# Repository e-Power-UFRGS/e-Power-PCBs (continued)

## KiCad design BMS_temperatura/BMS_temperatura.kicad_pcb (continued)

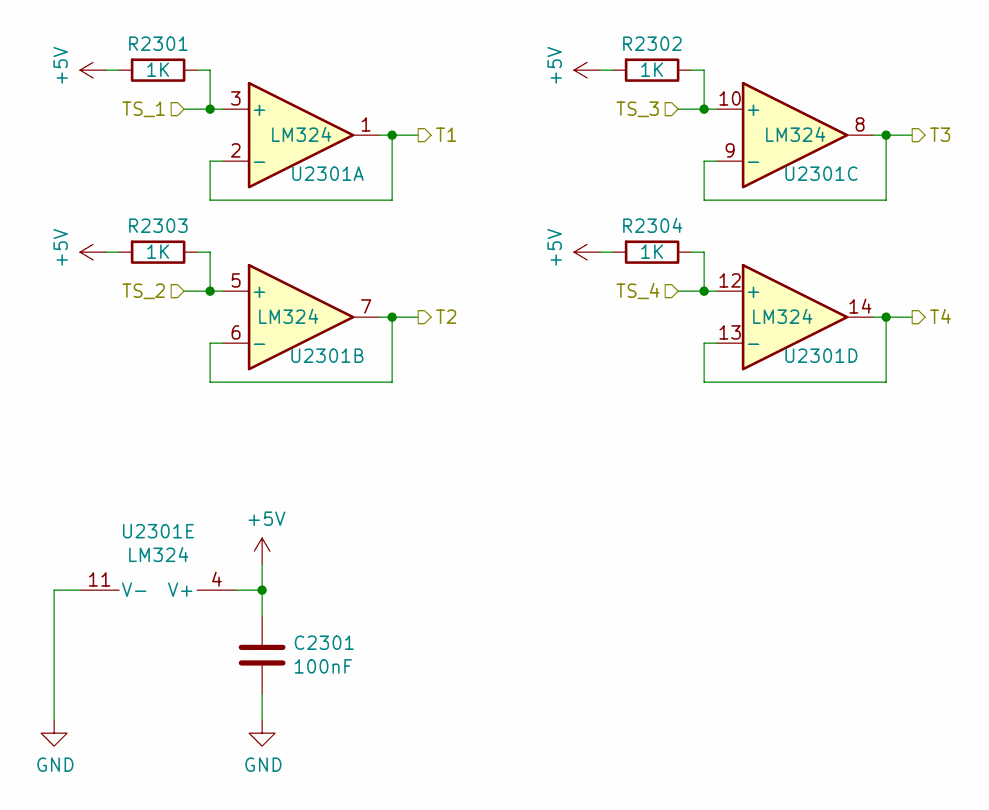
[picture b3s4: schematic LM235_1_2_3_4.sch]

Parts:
C2001: 100nF; C_0805_2012Metric; Voltage 50V; LCSC C49678
R2001, R2002, R2003, R2004: 1K; R_0805_2012Metric; Voltage 150V; LCSC C17513
U2001: LM324; SOIC-14_3.9x8.7mm_P1.27mm; LCSC C71035

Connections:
+5V: C2001.1, R2001.2, R2002.2, R2003.2, R2004.2, U2001.4 (V+); also elsewhere on the board
/T1: U2001.1, U2001.2 (-); also elsewhere on the board
/T2: U2001.6 (-), U2001.7; also elsewhere on the board
/T3: U2001.8, U2001.9 (-); also elsewhere on the board
/T4: U2001.13 (-), U2001.14; also elsewhere on the board
/Temperature Sensors/TS_1: R2001.1, U2001.3 (+); also elsewhere on the board
/Temperature Sensors/TS_2: R2003.1, U2001.5 (+); also elsewhere on the board
/Temperature Sensors/TS_3: R2002.1, U2001.10 (+); also elsewhere on the board
/Temperature Sensors/TS_4: R2004.1, U2001.12 (+); also elsewhere on the board
GND: C2001.2, U2001.11 (V-); also elsewhere on the board

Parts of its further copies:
C1801, C1901, C2101, C2201, C2301: 100nF; C_0805_2012Metric; Voltage 50V; LCSC C49678
R1801, R1802, R1803, R1804, R1901, R1902, R1903, R1904, R2101, R2102, R2103, R2104, R2201, R2202, R2203, R2204, R2301, R2302, R2303, R2304: 1K; R_0805_2012Metric; Voltage 150V; LCSC C17513
U1801, U1901, U2101, U2201, U2301: LM324; SOIC-14_3.9x8.7mm_P1.27mm; LCSC C71035

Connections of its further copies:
+5V: C1801.1, C1901.1, C2101.1, C2201.1, C2301.1, R1801.2, R1802.2, R1803.2, R1804.2, R1901.2, R1902.2, R1903.2, R1904.2, R2101.2, R2102.2, R2103.2, R2104.2, R2201.2, R2202.2, R2203.2, R2204.2, R2301.2, R2302.2, R2303.2, R2304.2, U1801.4 (V+), U1901.4 (V+), U2101.4 (V+), U2201.4 (V+), U2301.4 (V+); also elsewhere on the board
/T5: U1801.1, U1801.2 (-); also elsewhere on the board
/T6: U1801.6 (-), U1801.7; also elsewhere on the board
/T7: U1801.8, U1801.9 (-); also elsewhere on the board
/T8: U1801.13 (-), U1801.14; also elsewhere on the board
/T9: U1901.1, U1901.2 (-); also elsewhere on the board
/T10: U1901.6 (-), U1901.7; also elsewhere on the board
/T11: U1901.8, U1901.9 (-); also elsewhere on the board
/T12: U1901.13 (-), U1901.14; also elsewhere on the board
/T13: U2101.1, U2101.2 (-); also elsewhere on the board
/T14: U2101.6 (-), U2101.7; also elsewhere on the board
/T15: U2101.8, U2101.9 (-); also elsewhere on the board
/T16: U2101.13 (-), U2101.14; also elsewhere on the board
/T17: U2201.1, U2201.2 (-); also elsewhere on the board
/T18: U2201.6 (-), U2201.7; also elsewhere on the board
/T19: U2201.8, U2201.9 (-); also elsewhere on the board
/T20: U2201.13 (-), U2201.14; also elsewhere on the board
/T21: U2301.1, U2301.2 (-); also elsewhere on the board
/T22: U2301.6 (-), U2301.7; also elsewhere on the board
/T23: U2301.8, U2301.9 (-); also elsewhere on the board
/T24: U2301.13 (-), U2301.14; also elsewhere on the board
/Temperature Sensors/TS_5: R1801.1, U1801.3 (+); also elsewhere on the board
/Temperature Sensors/TS_6: R1803.1, U1801.5 (+); also elsewhere on the board
/Temperature Sensors/TS_7: R1802.1, U1801.10 (+); also elsewhere on the board
/Temperature Sensors/TS_8: R1804.1, U1801.12 (+); also elsewhere on the board
/Temperature Sensors/TS_9: R1901.1, U1901.3 (+); also elsewhere on the board
/Temperature Sensors/TS_10: R1903.1, U1901.5 (+); also elsewhere on the board
/Temperature Sensors/TS_11: R1902.1, U1901.10 (+); also elsewhere on the board
/Temperature Sensors/TS_12: R1904.1, U1901.12 (+); also elsewhere on the board
/Temperature Sensors/TS_13: R2101.1, U2101.3 (+); also elsewhere on the board
/Temperature Sensors/TS_14: R2103.1, U2101.5 (+); also elsewhere on the board
/Temperature Sensors/TS_15: R2102.1, U2101.10 (+); also elsewhere on the board
/Temperature Sensors/TS_16: R2104.1, U2101.12 (+); also elsewhere on the board
/Temperature Sensors/TS_17: R2201.1, U2201.3 (+); also elsewhere on the board
/Temperature Sensors/TS_18: R2203.1, U2201.5 (+); also elsewhere on the board
/Temperature Sensors/TS_19: R2202.1, U2201.10 (+); also elsewhere on the board
/Temperature Sensors/TS_20: R2204.1, U2201.12 (+); also elsewhere on the board
/Temperature Sensors/TS_21: R2301.1, U2301.3 (+); also elsewhere on the board
/Temperature Sensors/TS_22: R2303.1, U2301.5 (+); also elsewhere on the board
/Temperature Sensors/TS_23: R2302.1, U2301.10 (+); also elsewhere on the board
/Temperature Sensors/TS_24: R2304.1, U2301.12 (+); also elsewhere on the board
GND: C1801.2, C1901.2, C2101.2, C2201.2, C2301.2, U1801.11 (V-), U1901.11 (V-), U2101.11 (V-), U2201.11 (V-), U2301.11 (V-); also elsewhere on the board

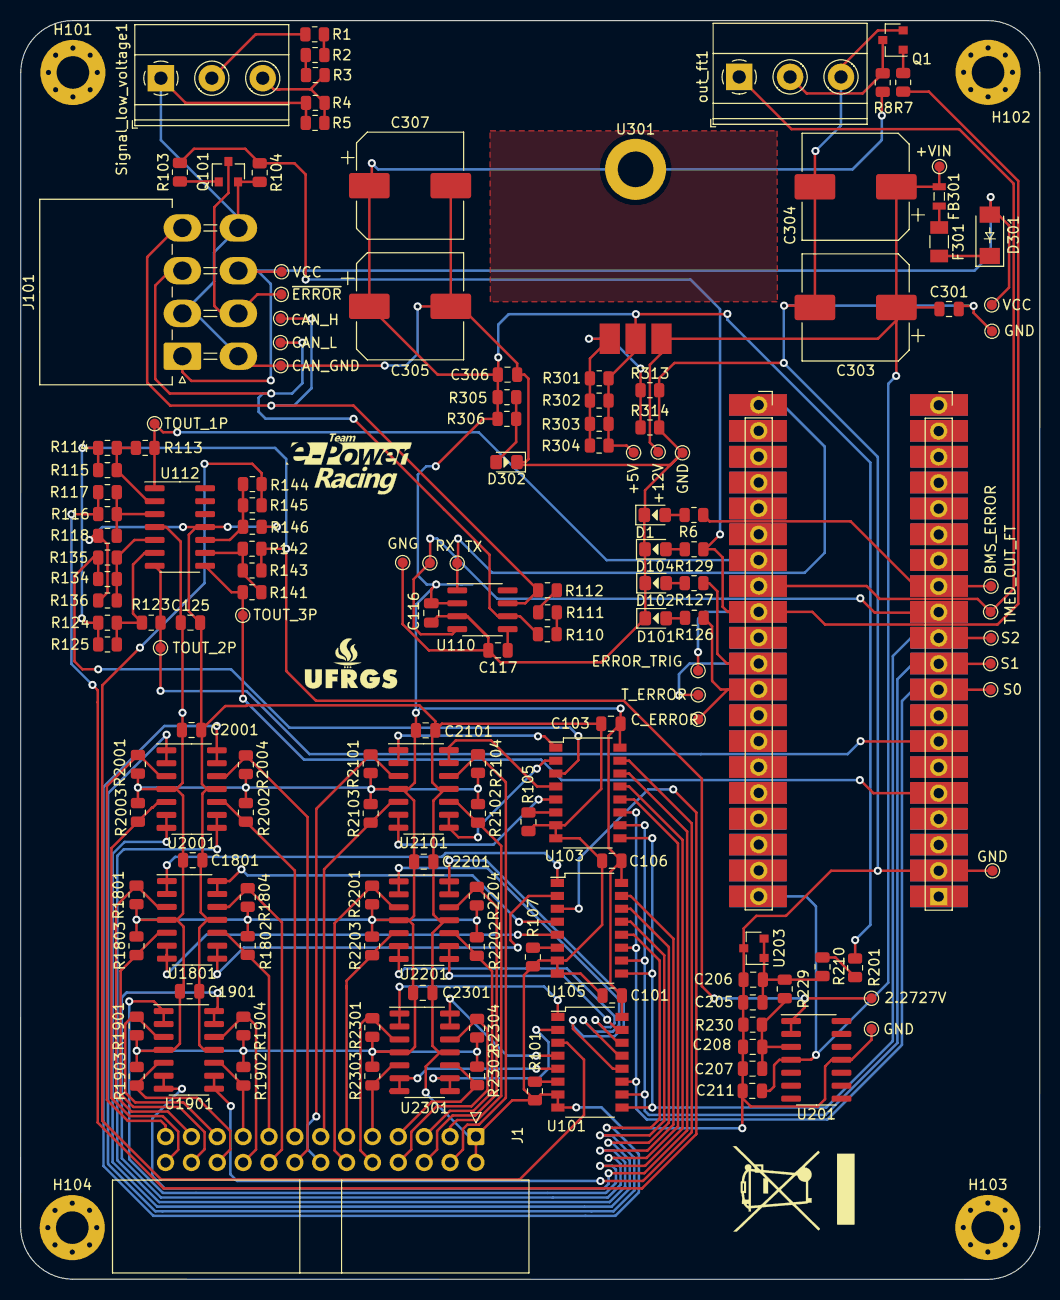
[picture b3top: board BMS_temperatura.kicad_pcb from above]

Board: 2 copper layers, 100.1 x 123.6 mm, 160 parts (0 on the bottom side), 102 nets.

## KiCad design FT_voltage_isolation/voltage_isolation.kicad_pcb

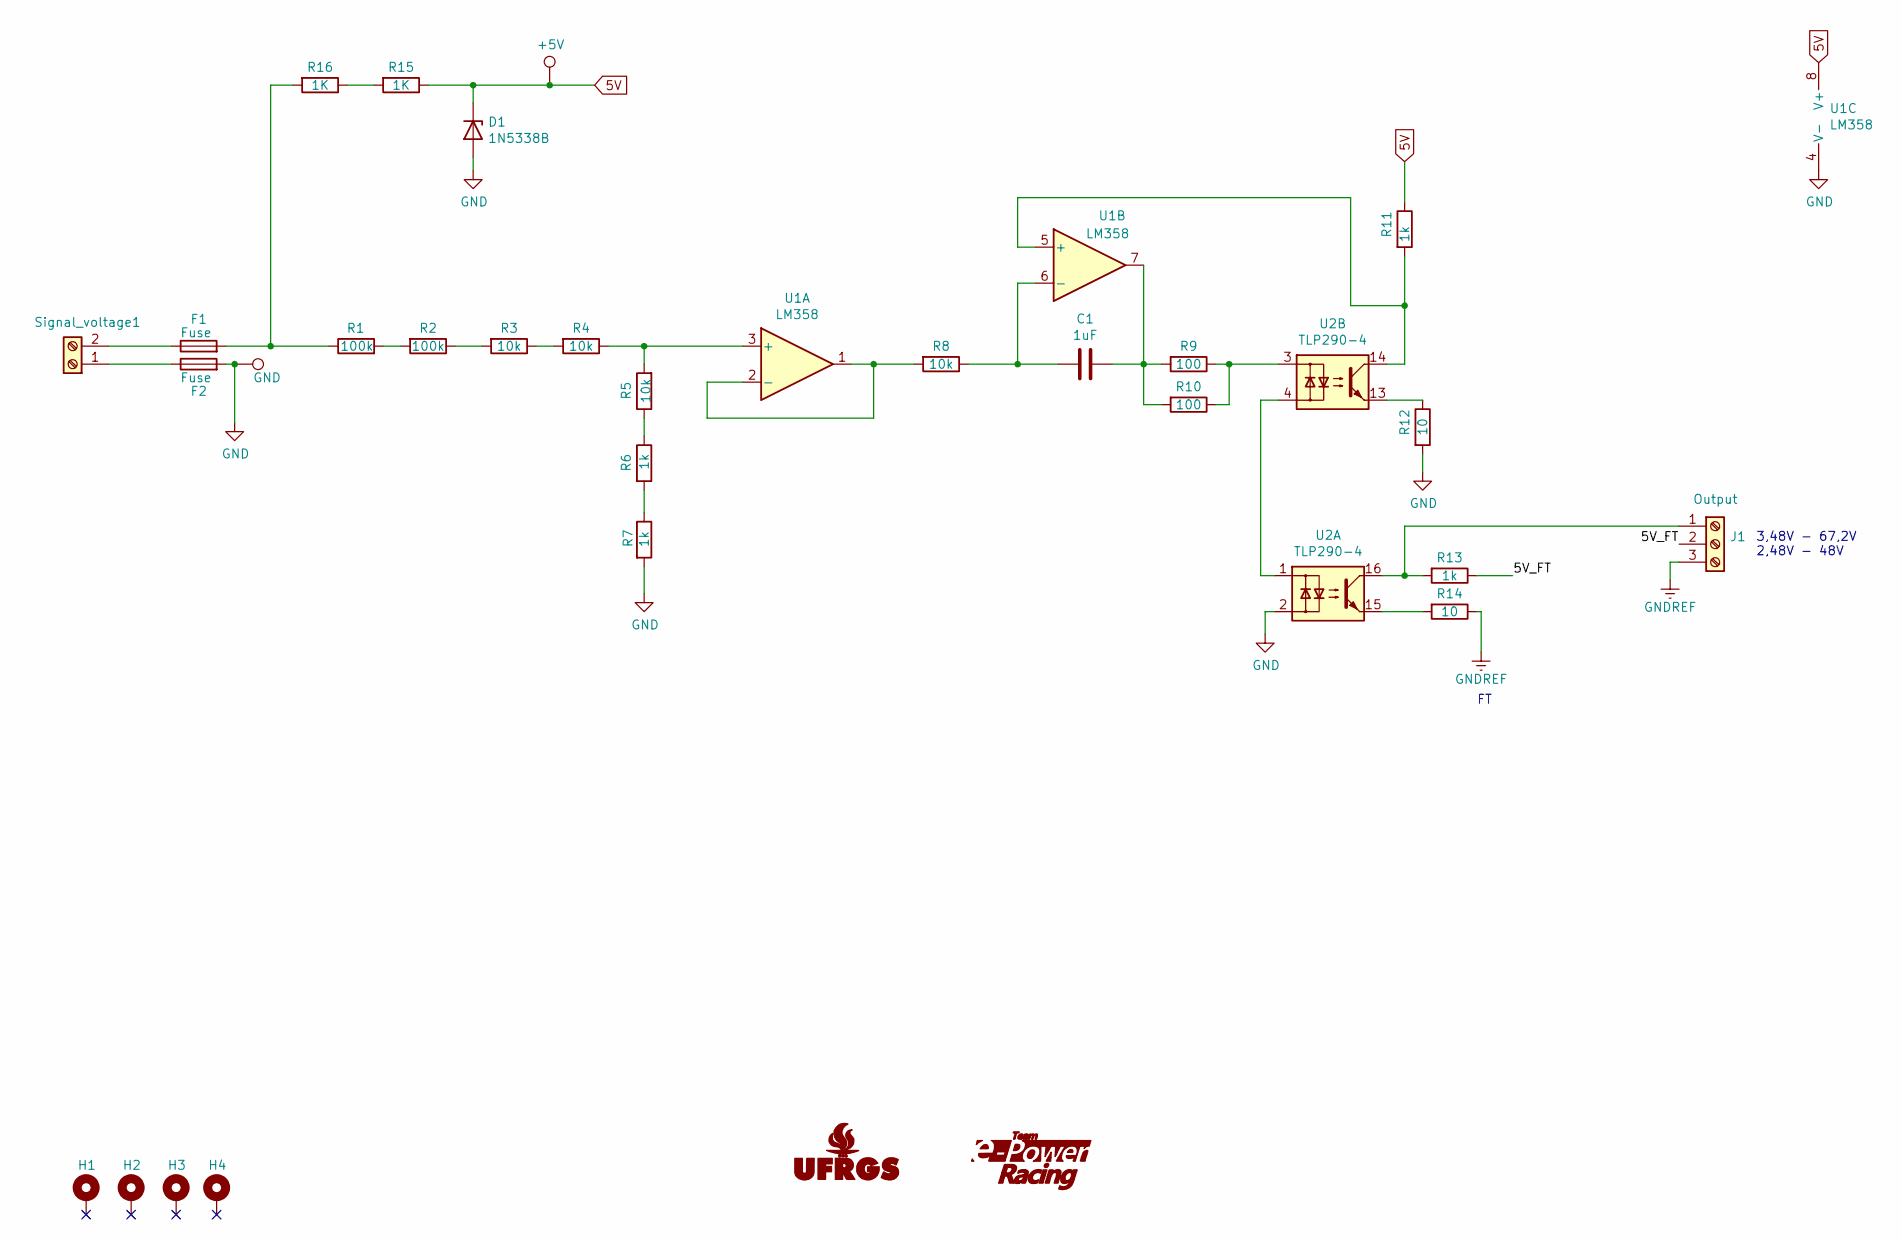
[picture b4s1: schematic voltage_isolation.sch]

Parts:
C1: 1uF; C_0805_2012Metric
D1: 1N5338B; D_DO-201_P15.24mm_Horizontal
F1, F2: Fuse; FUSE_1206_3216Metric
G1: Logo_UFRGS_Large; Logo_UFRGS_14.7x8.0mm_SilkS
G2: Logo_e-Power_Large; Logo_e-Power_16.5x8.0mm_SilkS
H1, H2, H3, H4: MountingHole_Pad; MountingHole_3.2mm_M3_Pad_Via
J1: Output; TerminalBlock_Phoenix_MKDS-1,5-3_1x03_P5.00mm_Horizontal
R1, R2: 100k; R_0805_2012Metric
R3, R4, R5, R8: 10k; R_0805_2012Metric
R6, R7, R11, R13: 1k; R_0805_2012Metric
R9, R10: 100; R_0805_2012Metric
R12, R14: 10; R_0805_2012Metric
R15, R16: 1K; R_Axial_DIN0207_L6.3mm_D2.5mm_P10.16mm_Horizontal
Signal_voltage1: Screw_Terminal_01x02; TerminalBlock_Phoenix_MKDS-1,5-2_1x02_P5.08mm_Horizontal
TP1: +5V; TestPoint_Pad_D1.0mm
TP2: GND; TestPoint_Pad_D1.0mm
U1: LM358; SOIC-8_3.9x4.9mm_P1.27mm
U2: TLP290-4; SOIC-16_4.55x10.3mm_P1.27mm(TLP290-4)

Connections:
5V: D1.1 (K), R11.1, R15.1, TP1.1, U1.8 (V+)
/5V_FT: J1.2, R13.1
GND: D1.2 (A), F2.2, R7.2, R12.2, TP2.1, U1.4 (V-), U2.2
GNDREF: J1.3, R14.1
unnamed: C1.1, R9.2, R10.2, U1.7
unnamed: C1.2, R8.1, U1.6 (-)
unnamed: F1.1, Signal_voltage1.2
unnamed: F1.2, R1.1, R16.2
unnamed: F2.1, Signal_voltage1.1
unnamed: J1.1, R13.2, U2.16
unnamed: R1.2, R2.2
unnamed: R2.1, R3.2
unnamed: R3.1, R4.2
unnamed: R4.1, R5.2, U1.3 (+)
unnamed: R5.1, R6.1
unnamed: R6.2, R7.1
unnamed: R8.2, U1.1, U1.2 (-)
unnamed: R9.1, R10.1, U2.3
unnamed: R11.2, U1.5 (+), U2.14
unnamed: R12.1, U2.13
unnamed: R14.2, U2.15
unnamed: R15.2, R16.1
unnamed: U2.1, U2.4

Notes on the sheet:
3,48V - 67,2V 2,48V - 48V

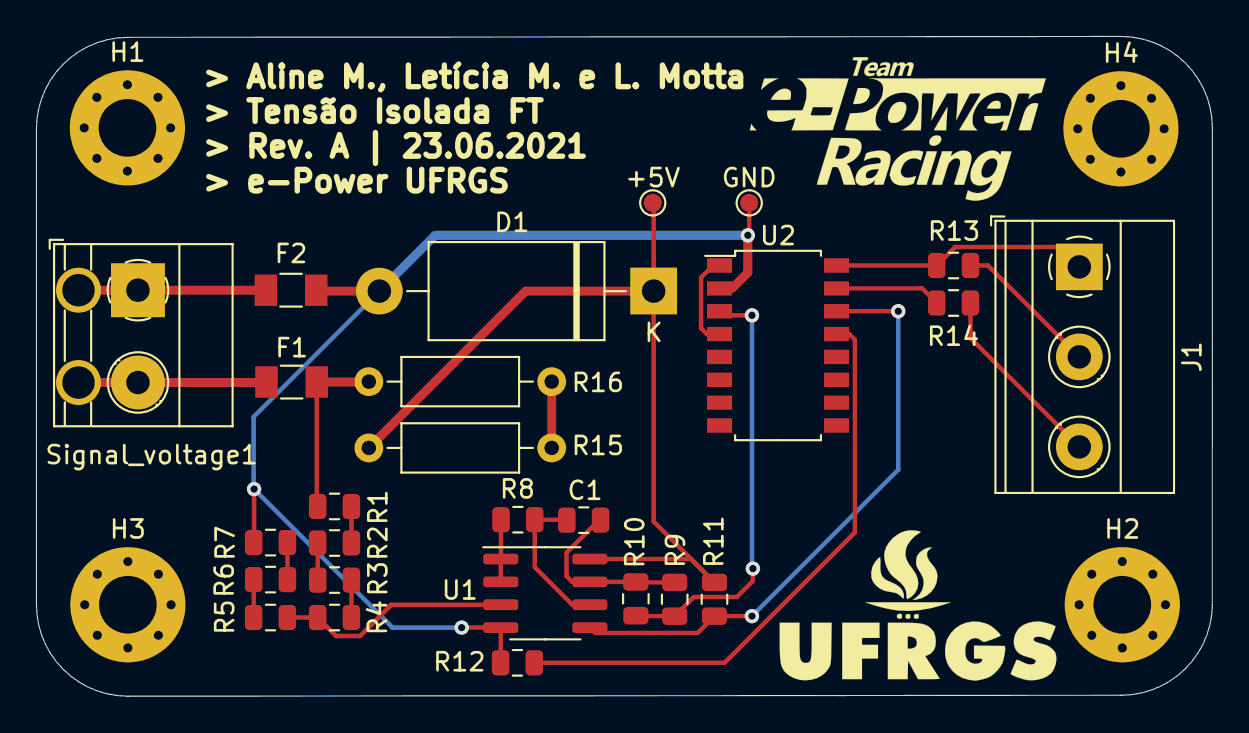
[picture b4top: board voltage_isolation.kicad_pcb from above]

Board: 2 copper layers, 65.3 x 36.7 mm, 32 parts (0 on the bottom side), 23 nets.
